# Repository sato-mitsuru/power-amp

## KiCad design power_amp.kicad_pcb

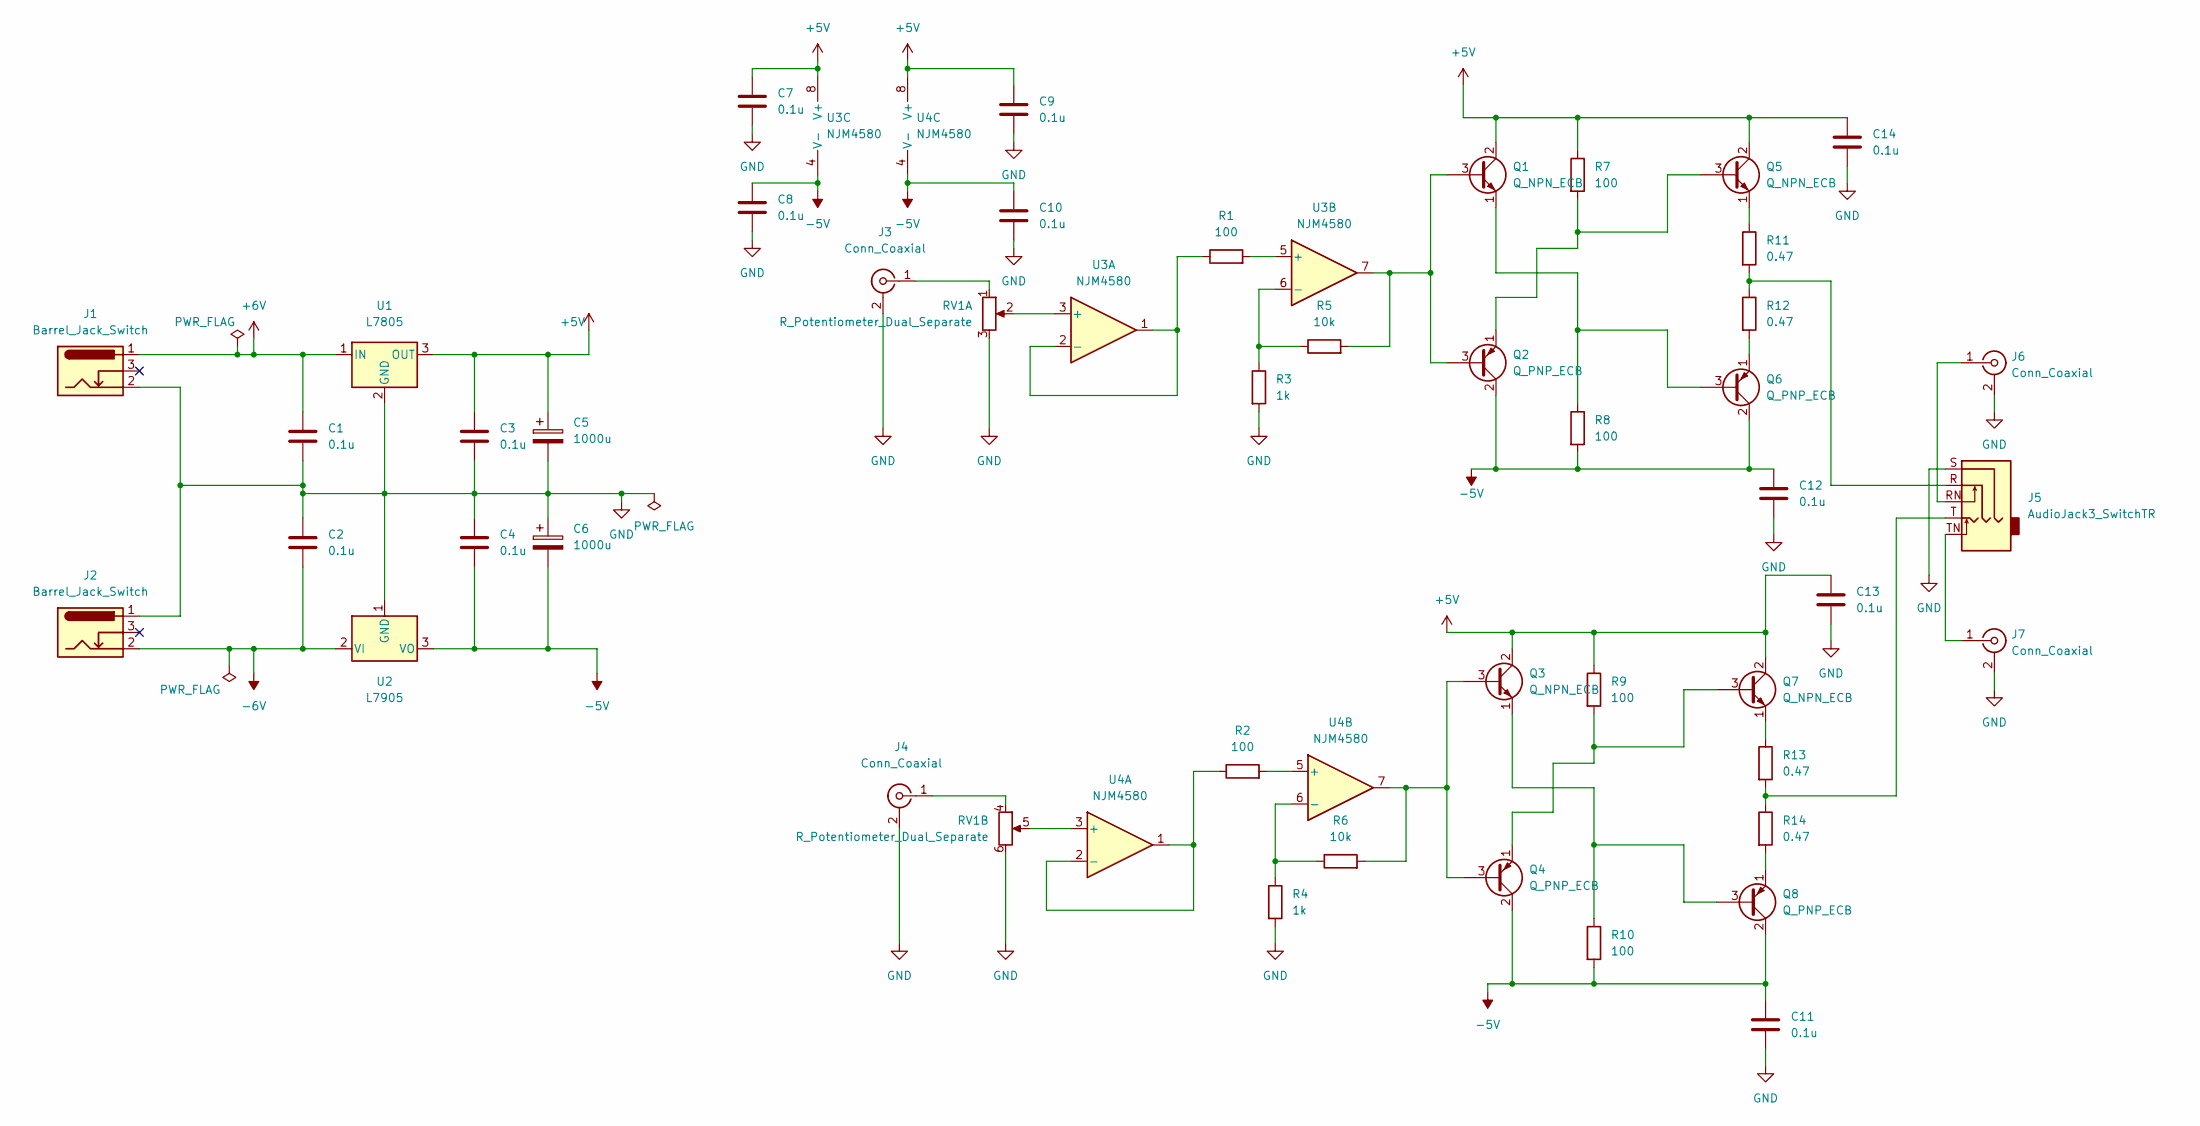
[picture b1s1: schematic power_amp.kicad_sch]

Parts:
C1, C2, C3, C4, C7, C8, C9, C10, C11, C12, C13, C14: 0.1u; C_Disc_D5.0mm_W2.5mm_P5.00mm
C5, C6: 1000u; C_Radial_D12.5mm_H20.0mm_P5.00mm
J1, J2: Barrel_Jack_Switch; BarrelJack_Horizontal
J3, J4, J6, J7: Conn_Coaxial; MJ_523
J5: AudioJack3_SwitchTR; Jack_3.5mm_Ledino_KB3SPRS_Horizontal
Q1, Q3, Q5, Q7: Q_NPN_ECB; TO-126-3_Vertical
Q2, Q4, Q6, Q8: Q_PNP_ECB; TO-126-3_Vertical
R1, R2, R7, R8, R9, R10: 100; R_Axial_DIN0309_L9.0mm_D3.2mm_P12.70mm_Horizontal
R3, R4: 1k; R_Axial_DIN0309_L9.0mm_D3.2mm_P12.70mm_Horizontal
R5, R6: 10k; R_Axial_DIN0309_L9.0mm_D3.2mm_P12.70mm_Horizontal
R11, R12, R13, R14: 0.47; R_Axial_DIN0309_L9.0mm_D3.2mm_P12.70mm_Horizontal
RV1: R_Potentiometer_Dual_Separate; 2_volume
U1: L7805; TO-220-3_Vertical
U2: L7905; TO-220-3_Vertical
U3, U4: NJM4580; DIP-8_W7.62mm_Socket

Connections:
+5V: C3.1, C5.1, C7.1, C9.1, C13.1, C14.1, Q1.2 (C), Q3.2 (C), Q5.2 (C), Q7.2 (C), R7.1, R9.1, U1.3 (OUT), U3.8 (V+), U4.8 (V+)
+6V: C1.1, J1.1, U1.1 (IN)
-5V: C4.2, C6.2, C8.1, C10.1, C11.1, C12.1, Q2.2 (C), Q4.2 (C), Q6.2 (C), Q8.2 (C), R8.2, R10.2, U2.3 (VO), U3.4 (V-), U4.4 (V-)
-6V: C2.2, J2.2, U2.2 (VI)
GND: C1.2, C2.1, C3.2, C4.1, C5.2, C6.1, C7.2, C8.2, C9.2, C10.2, C11.2, C12.2, C13.2, C14.2, J1.2, J2.1, J3.2 (Ext), J4.2 (Ext), J5.S, J6.2 (Ext), J7.2 (Ext), R3.2, R4.2, RV1.3, RV1.6, U1.2 (GND), U2.1 (GND); also elsewhere on the board
unnamed: J3.1 (In), RV1.1
unnamed: J4.1 (In), RV1.4
unnamed: J5.R, R11.2, R12.1
unnamed: J5.RN, J6.1 (In)
unnamed: J5.T, R13.2, R14.1
unnamed: J5.TN, J7.1 (In)
unnamed: Q1.1 (E), Q6.3 (B), R8.1
unnamed: Q1.3 (B), Q2.3 (B), R5.2, U3.7
unnamed: Q3.1 (E), Q8.3 (B), R10.1
unnamed: Q3.3 (B), Q4.3 (B), R6.2, U4.7
unnamed: Q5.1 (E), R11.1
unnamed: Q2.1 (E), Q5.3 (B), R7.2
unnamed: Q6.1 (E), R12.2
unnamed: Q7.1 (E), R13.1
unnamed: Q4.1 (E), Q7.3 (B), R9.2
unnamed: Q8.1 (E), R14.2
unnamed: R1.1, U3.1, U3.2 (-)
unnamed: R1.2, U3.5 (+)
unnamed: R2.1, U4.1, U4.2 (-)
unnamed: R2.2, U4.5 (+)
unnamed: R3.1, R5.1, U3.6 (-)
unnamed: R4.1, R6.1, U4.6 (-)
unnamed: RV1.2, U3.3 (+)
unnamed: RV1.5, U4.3 (+)

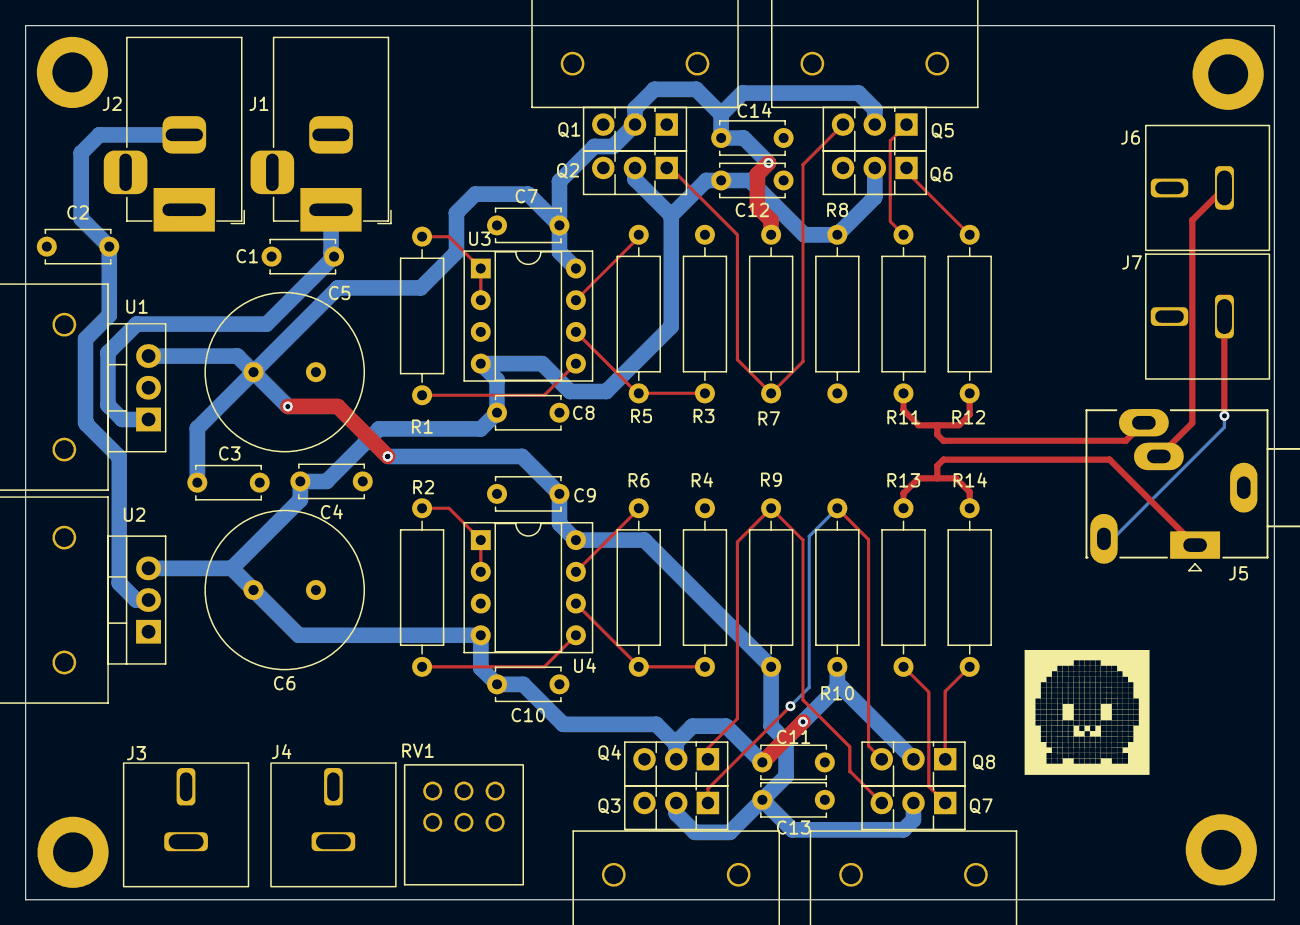
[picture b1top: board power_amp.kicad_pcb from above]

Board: 2 copper layers, 100.0 x 70.0 mm, 52 parts (0 on the bottom side), 29 nets.

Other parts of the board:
REF1, REF2, REF3, REF4: MountingHole_3.2mm_M3_ISO7380_Pad

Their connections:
GND: REF1.1, REF2.1, REF3.1, REF4.1; also elsewhere on the board

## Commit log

2022-12-13 1st commit
2022-12-13 made power-line thick
2022-12-14 made -5V line thick
2022-12-14 made power-line 1mm
